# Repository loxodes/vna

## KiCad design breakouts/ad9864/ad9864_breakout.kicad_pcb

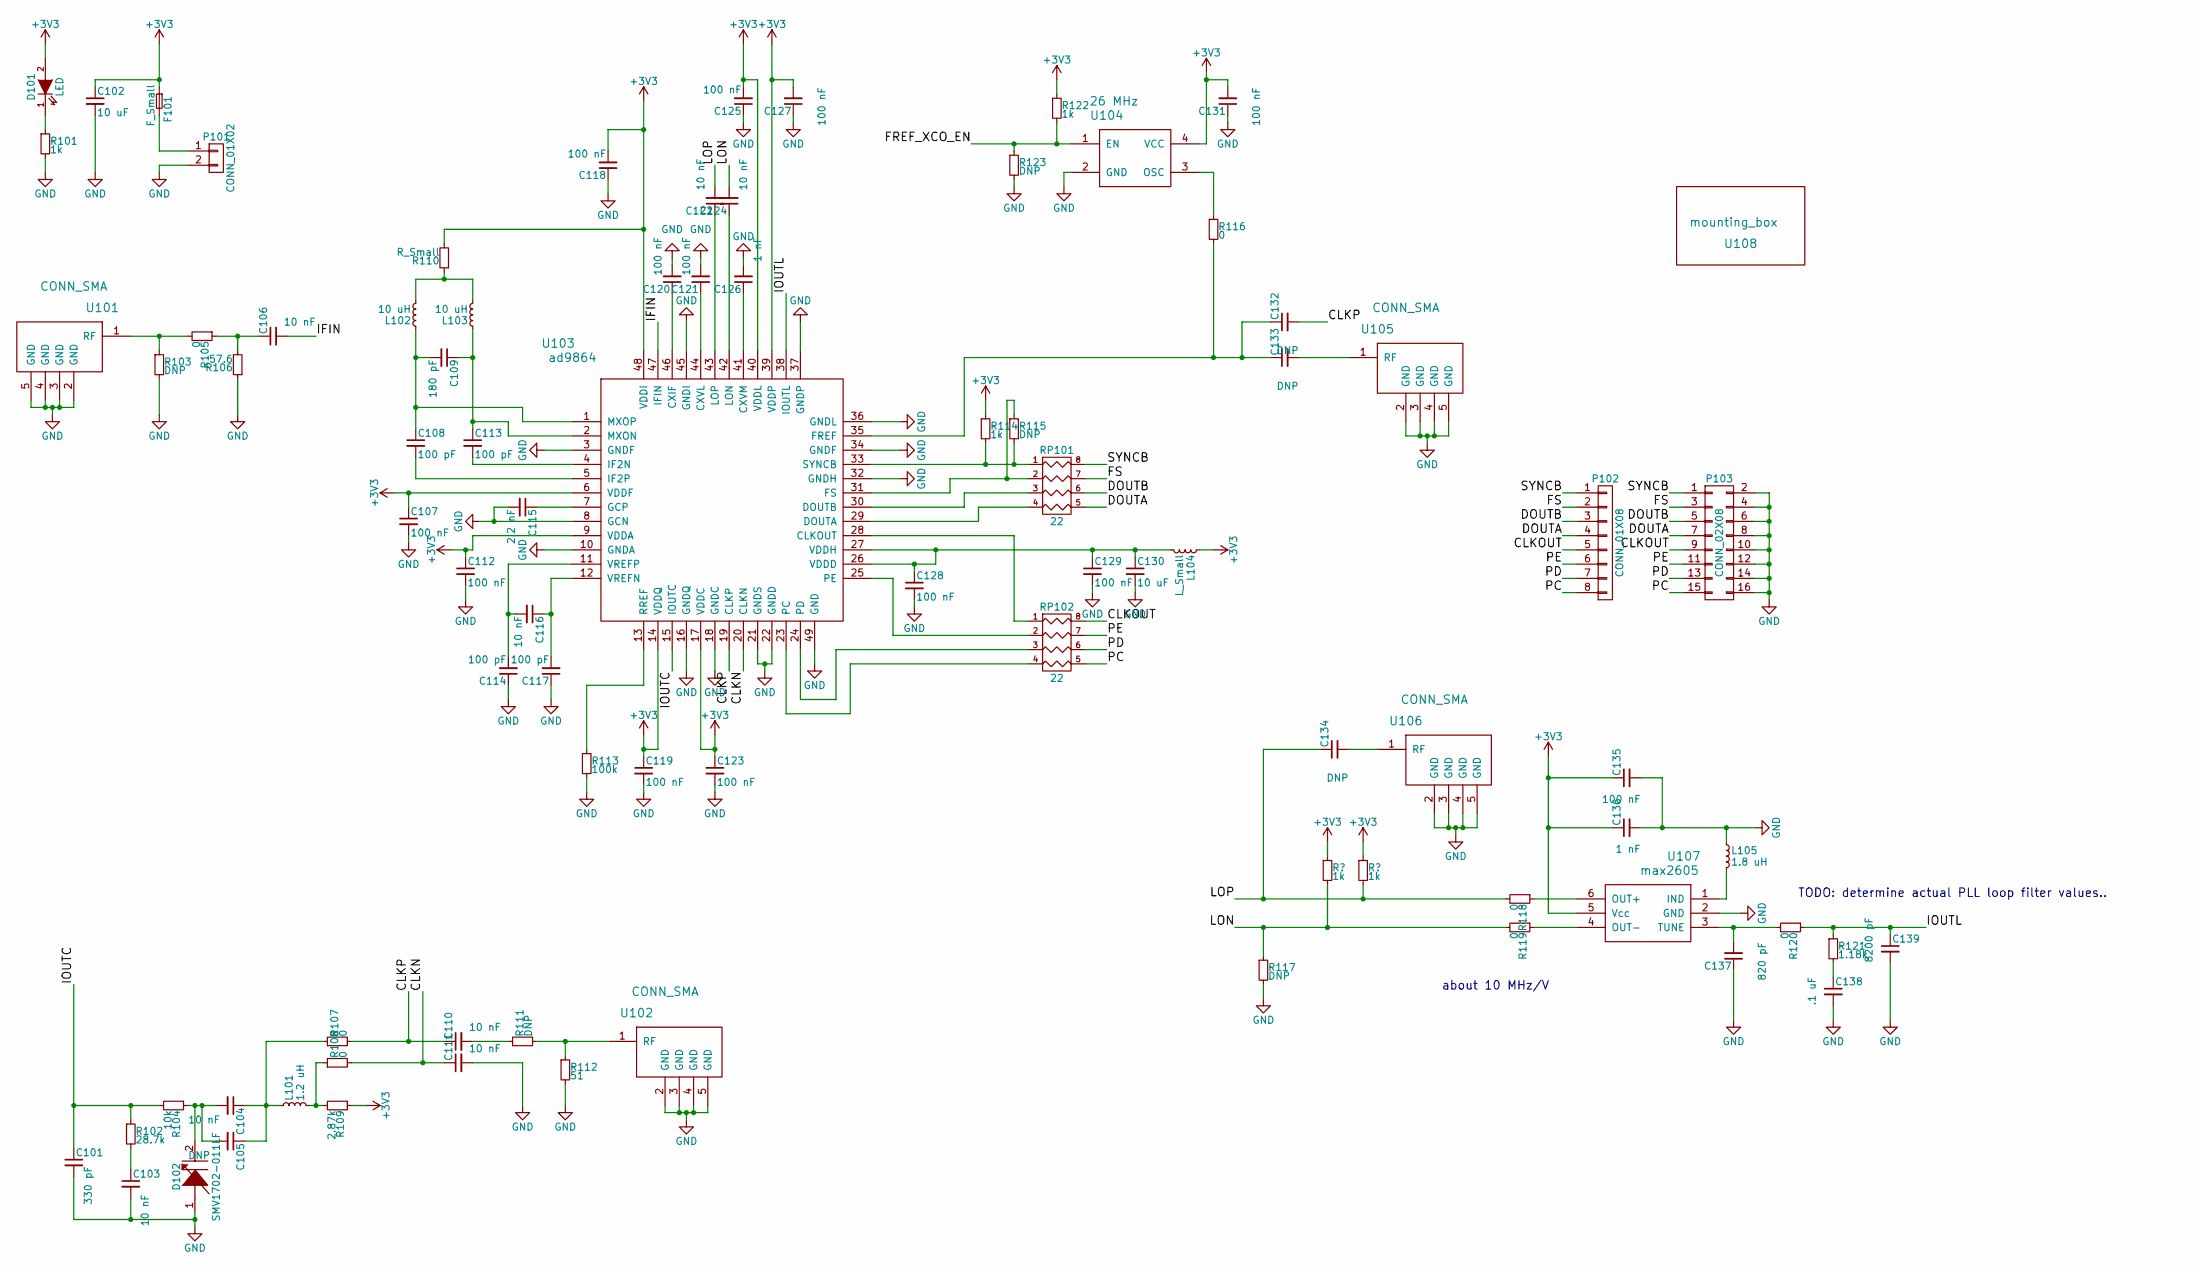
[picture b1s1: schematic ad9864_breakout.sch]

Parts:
C101: 330 pF; C_0603
C102, C130: 10 uF; C_0805
C103, C104, C106, C110, C111, C116, C122, C124: 10 nF; C_0603
C105, C132, C133, C134: DNP; C_0603
C107, C112, C118, C119, C120, C121, C123, C125, C127, C128, C129, C131, C135: 100 nF; C_0603
C108, C113, C114, C117: 100 pF; C_0603
C109: 180 pF; C_0603
C115: 2.2 nF; C_0603
C126, C136: 1 nF; C_0603
C137: 820 pF; C_0603
C138: .1 uF; C_0603
C139: 8200 pF; C_0603
D101: LED; LED_0603
D102: SMV1702-011LF; SOD-323
F101: F_Small; R_1812
L101: 1.2 uH; R_0805
L102, L103: 10 uH; R_0805
L104: L_Small; R_0603
L105: 1.8 uH; R_0805
P101: CONN_01X02; TerminalBlock_Pheonix_PT-3.5mm_2pol
P102: CONN_01X08; Pin_Header_Straight_1x08
P103: CONN_02X08; Pin_Header_Straight_2x08
R101, R114, R122: 1k; R_0603
R102: 28.7k; R_0603
R103, R111, R115, R117, R123: DNP; R_0603
R104: 10k; R_0603
R105, R107, R108, R116, R118, R119, R120: 0; R_0603
R106: 57.6; R_0603
R109: 2.87k; R_0603
R110: R_Small; R_0603
R112: 51; R_0603
R113: 100k; R_0603
R121: 1.18k; R_0603
RP101, RP102: 22; R_Array_Concave_4x0603
U101, U102, U105, U106: CONN_SMA; 732512200_SMA
U103: ad9864; QFN-48-1EP_7x7mm_Pitch0.5mm
U104: 26 MHz; crystal_FA238-TSX3225
U107: max2605; SOT-23-6
U108: mounting_box; momo

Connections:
+3V3: C102.1, C107.1, C112.1, C118.2, C119.1, C123.1, C125.2, C127.2, C131.2, C135.1, C136.1, D101.2 (A), F101.1, L104.1, R109.1, R110.2, R114.1, R122.1, U103.6 (VDDF), U103.9 (VDDA), U103.14 (VDDQ), U103.17 (VDDC), U103.39 (VDDP), U103.40 (VDDL), U103.48 (VDDI), U104.4 (VCC), U107.5 (Vcc)
/CLKN: C111.1, R108.2, U103.20 (CLKN)
/CLKOUT: P102.5, P103.9, RP102.8 (R1)
/CLKP: C110.1, C132.2, R107.2, U103.19 (CLKP)
/DOUTA: P102.4, P103.7, RP101.5 (R4)
/DOUTB: P102.3, P103.5, RP101.6 (R3)
/FREF_XCO_EN: R122.2, R123.1, U104.1 (EN)
/FS: P102.2, P103.3, RP101.7 (R2)
/IFIN: C106.2, U103.47 (IFIN)
/IOUTC: C101.1, R102.1, R104.2, U103.15 (IOUTC)
/IOUTL: C139.1, R120.1, R121.1, U103.38 (IOUTL)
/LON: C124.2, R117.1, R119.2
/LOP: C122.2, C134.1, R118.2
/PC: P102.8, P103.15, RP102.5 (R4)
/PD: P102.7, P103.13, RP102.6 (R3)
/PE: P102.6, P103.11, RP102.7 (R2)
/SYNCB: P102.1, P103.1, RP101.8 (R1)
GND: C101.2, C102.2, C103.2, C107.2, C111.2, C112.2, C114.1, C115.2, C117.1, C118.1, C119.2, C120.2, C121.2, C123.2, C125.1, C126.2, C127.1, C128.2, C129.2, C130.2, C131.1, C135.2, C136.2, C137.1, C138.2, C139.2, D102.1 (ANODE), L105.1, P101.2, P103.2, P103.4, P103.6, P103.8, P103.10, P103.12, P103.14, P103.16, R101.2, R103.2, R106.1, R112.2, R113.2, R117.2, R123.2, U101.2 (GND), U101.3 (GND), U101.4 (GND), U101.5 (GND), U102.2 (GND), U102.3 (GND), U102.4 (GND), U102.5 (GND), U103.3 (GNDF), U103.8 (GCN), U103.10 (GNDA), U103.16 (GNDQ), U103.18 (GNDC), U103.21 (GNDS), U103.22 (GNDD), U103.32 (GNDH), U103.34 (GNDF), U103.36 (GNDL), U103.37 (GNDP), U103.45 (GNDI), U103.49 (GND), U104.2 (GND), U105.2 (GND), U105.3 (GND), U105.4 (GND), U105.5 (GND), U106.2 (GND), U106.3 (GND), U106.4 (GND), U106.5 (GND), U107.2 (GND)
unnamed: C103.1, R102.2
unnamed: C104.1, C105.1, L101.1, R107.1
unnamed: C104.2, C105.2, D102.2 (CATHODE), R104.1
unnamed: C106.1, R105.1, R106.2
unnamed: C108.1, C109.2, L102.1, U103.1 (MXOP)
unnamed: C108.2, U103.5 (IF2P)
unnamed: C109.1, C113.1, L103.1, U103.2 (MXON)
unnamed: C110.2, R111.1
unnamed: C113.2, U103.4 (IF2N)
unnamed: C114.2, C116.2, U103.11 (VREFP)
unnamed: C115.1, U103.7 (GCP)
unnamed: C116.1, C117.2, U103.12 (VREFN)
unnamed: C120.1, U103.46 (CXIF)
unnamed: C121.1, U103.44 (CXVL)
unnamed: C122.1, U103.43 (LOP)
unnamed: C124.1, U103.42 (LON)
unnamed: C126.1, U103.41 (CXVM)
unnamed: C128.1, C129.1, C130.1, L104.2, U103.26 (VDDD), U103.27 (VDDH)
unnamed: C132.1, C133.1, R116.2, U103.35 (FREF)
unnamed: C133.2, U105.1 (RF)
unnamed: C134.2, U106.1 (RF)
unnamed: C137.2, R120.2, U107.3 (TUNE)
unnamed: C138.1, R121.2
unnamed: D101.1 (K), R101.1
unnamed: F101.2, P101.1
unnamed: L101.2, R108.1, R109.2
unnamed: L102.2, L103.2, R110.1
unnamed: L105.2, U107.1 (IND)
unnamed: R103.1, R105.2, U101.1 (RF)
unnamed: R111.2, R112.1, U102.1 (RF)
unnamed: R113.1, U103.13 (RREF)
unnamed: R114.2, R115.2, RP101.1, U103.33 (SYNCB)
unnamed: R115.1, RP101.2, U103.31 (FS)
unnamed: R116.1, U104.3 (OSC)
unnamed: R118.1, U107.6 (OUT+)
unnamed: R119.1, U107.4 (OUT-)
unnamed: RP101.3, U103.30 (DOUTB)
unnamed: RP101.4, U103.29 (DOUTA)
unnamed: RP102.1, U103.28 (CLKOUT)
unnamed: RP102.2, U103.25 (PE)
unnamed: RP102.3, U103.24 (PD)
unnamed: RP102.4, U103.23 (PC)

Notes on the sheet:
about 10 MHz/V
TODO: determine actual PLL loop filter values..

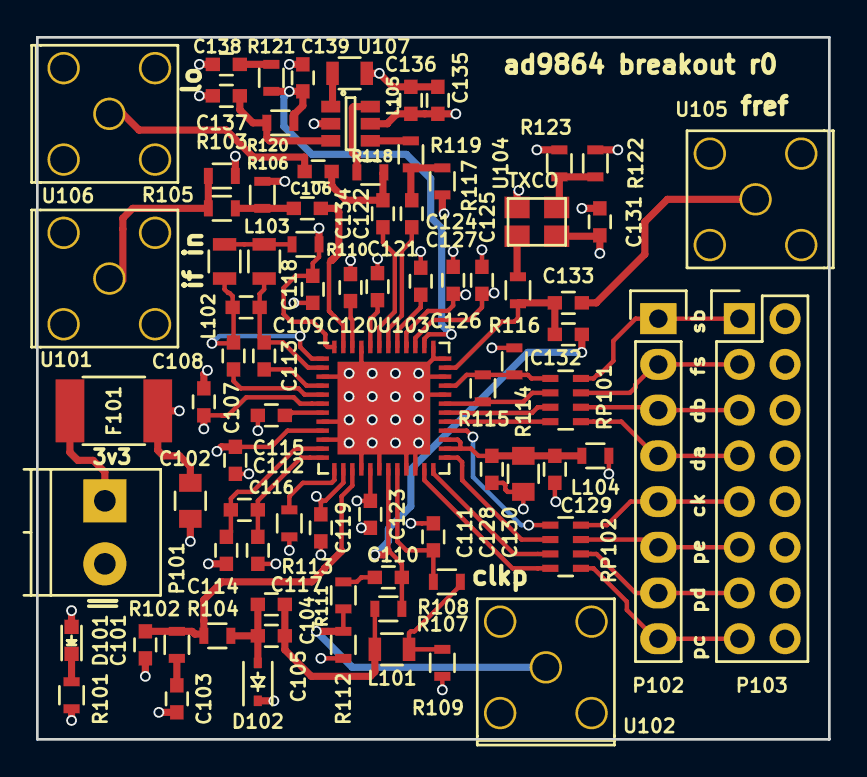
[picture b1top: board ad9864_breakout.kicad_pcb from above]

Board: 4 copper layers, 44.0 x 39.0 mm, 83 parts (1 on the bottom side), 60 nets.

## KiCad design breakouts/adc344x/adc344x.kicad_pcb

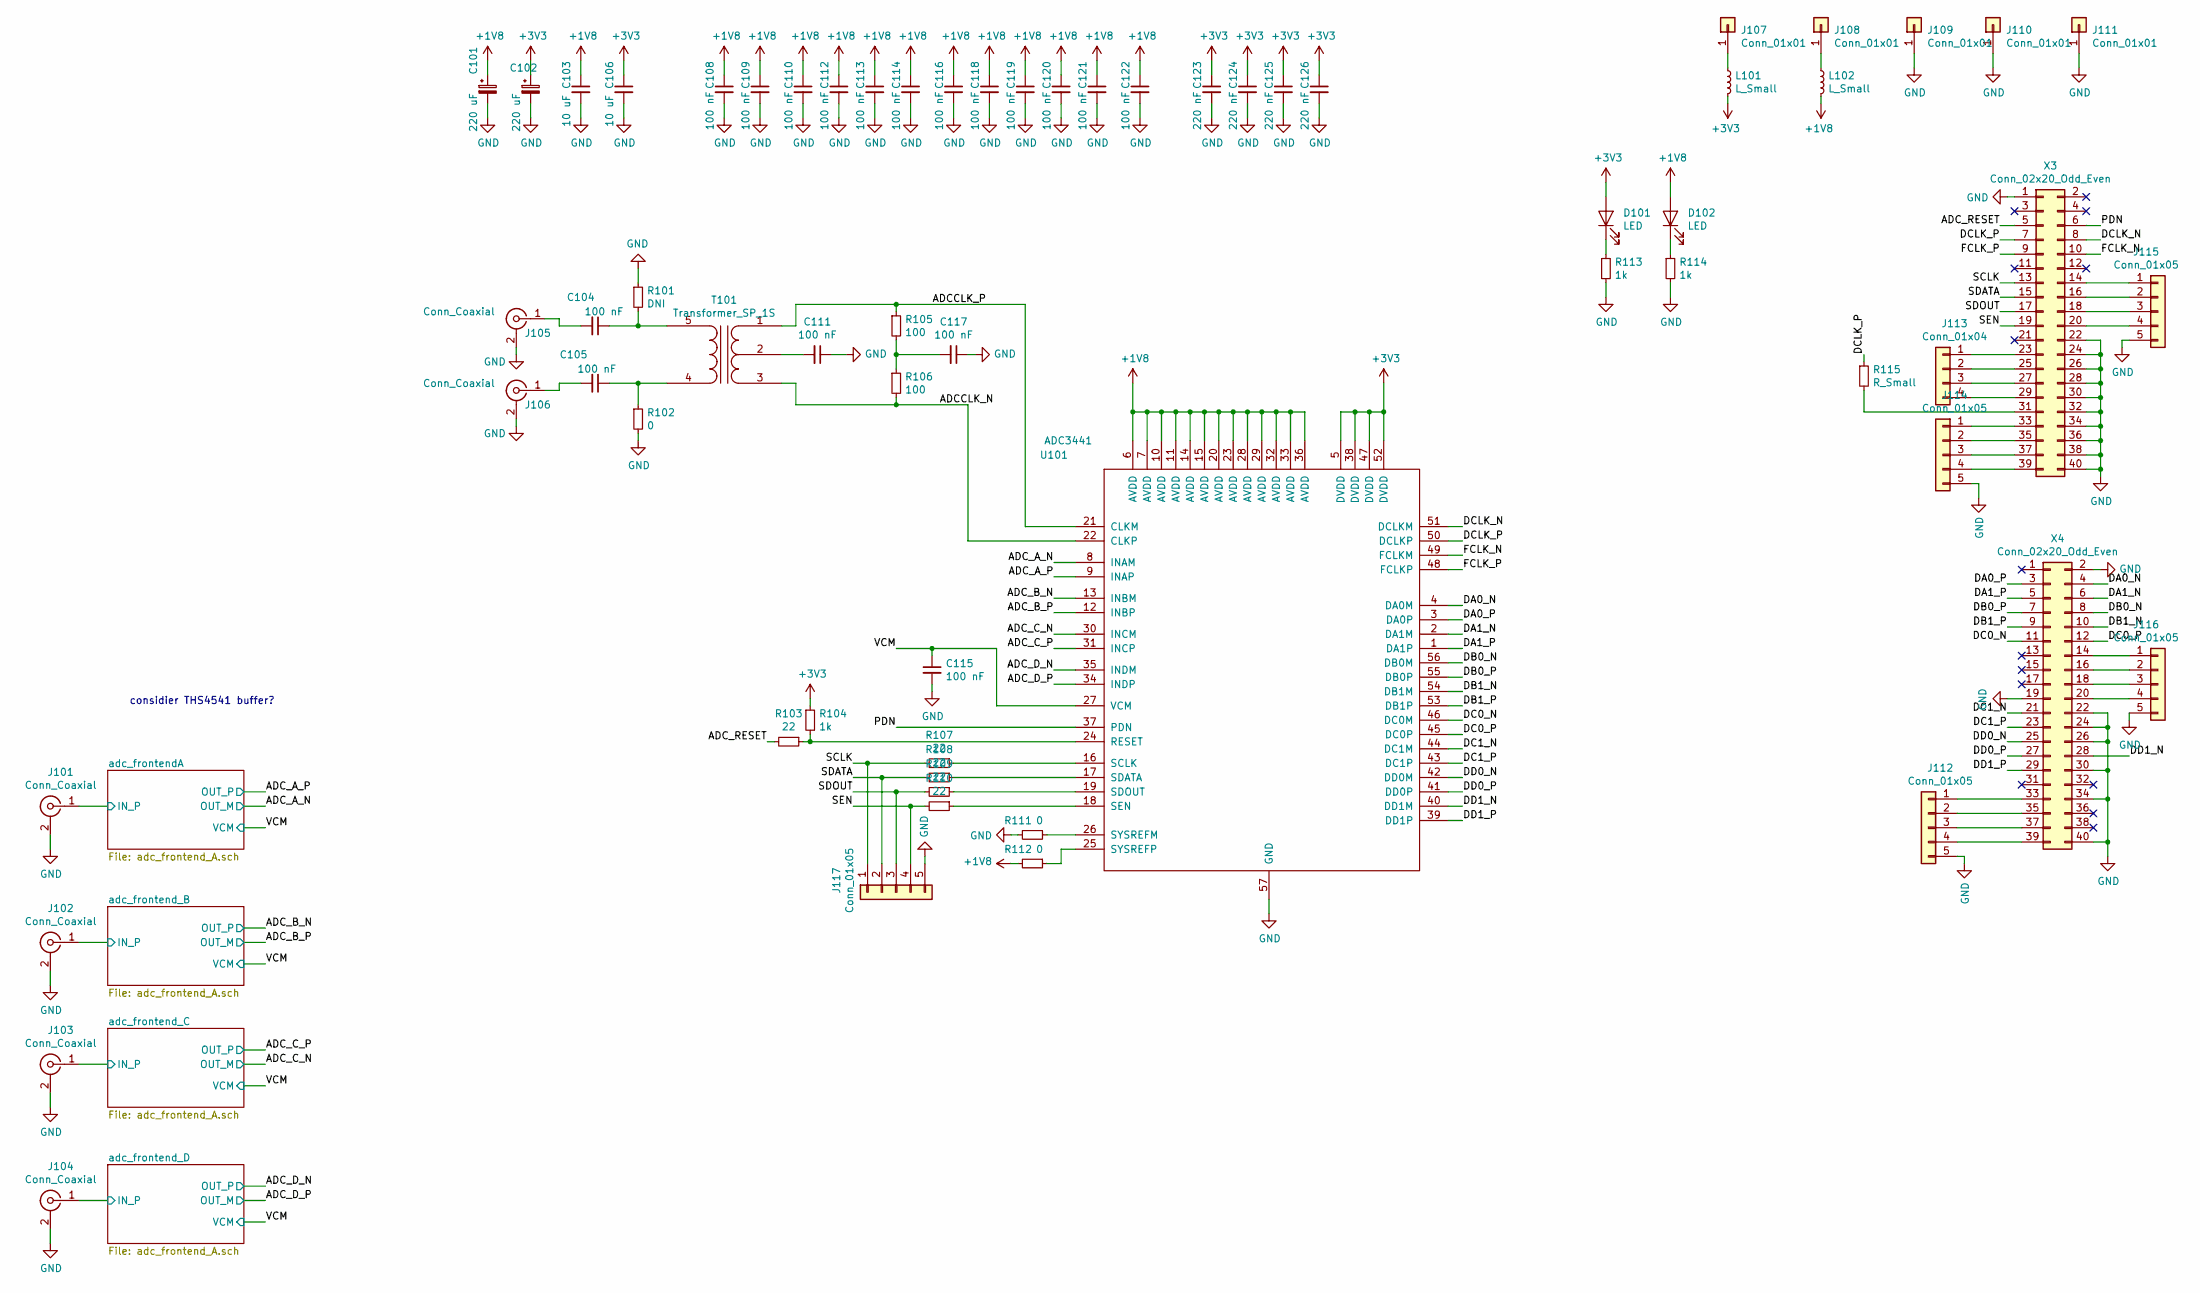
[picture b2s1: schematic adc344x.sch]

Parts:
C101, C102: 220 uF; c_elec_6.3x5.8
C103, C106: 10 uF; C_0603
C104, C105, C108, C109, C110, C111, C112, C113, C114, C115, C116, C117, C118, C119, C120, C121, C122: 100 nF; C_0402
C123, C124, C125, C126: 220 nF; C_0402
D101, D102: LED; LED_0603
J101, J102, J103, J104, J105, J106: Conn_Coaxial; 732512200_SMA
J107, J108, J109, J110, J111: Conn_01x01; TURRET_MILLMAX_2101
J112, J114, J115, J116, J117: Conn_01x05; Pin_Header_Straight_1x05
J113: Conn_01x04; Pin_Header_Straight_1x04
L101, L102: L_Small; R_0603
R101: DNI; R_0402
R102, R111, R112: 0; R_0402
R103, R107, R108, R109, R110: 22; R_0402
R104, R113, R114: 1k; R_0402
R105, R106: 100; R_0402
R115: R_Small; R_0402
T101: Transformer_SP_1S; 5LEAD_BALUN_4p83mm_3p3mm
U101: ADC3441; QFN-56_EP_8x8_Pitch0.5mm
X3, X4: Conn_02x20_Odd_Even; Pin_Header_Straight_2x20

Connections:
+1V8: C101.1, C103.1, C108.1, C109.1, C110.1, C112.1, C113.1, C114.1, C116.1, C118.1, C119.1, C120.1, C121.1, C122.1, D102.2 (A), L102.2, R112.2, U101.6 (AVDD), U101.7 (AVDD), U101.10 (AVDD), U101.11 (AVDD), U101.14 (AVDD), U101.15 (AVDD), U101.20 (AVDD), U101.23 (AVDD), U101.28 (AVDD), U101.29 (AVDD), U101.32 (AVDD), U101.33 (AVDD), U101.36 (AVDD)
+3V3: C102.1, C106.1, C123.1, C124.1, C125.1, C126.1, D101.2 (A), L101.2, R104.1, U101.5 (DVDD), U101.38 (DVDD), U101.47 (DVDD), U101.52 (DVDD)
/ADCCLK_N: R106.2, T101.3 (PR2), U101.22 (CLKP)
/ADCCLK_P: R105.1, T101.1 (PR1), U101.21 (CLKM)
/ADC_A_N: U101.8 (INAM); also elsewhere on the board
/ADC_A_P: U101.9 (INAP); also elsewhere on the board
/ADC_B_N: U101.13 (INBM); also elsewhere on the board
/ADC_B_P: U101.12 (INBP); also elsewhere on the board
/ADC_C_N: U101.30 (INCM); also elsewhere on the board
/ADC_C_P: U101.31 (INCP); also elsewhere on the board
/ADC_D_N: U101.35 (INDM); also elsewhere on the board
/ADC_D_P: U101.34 (INDP); also elsewhere on the board
/ADC_RESET: R103.2, X3.5
/DA0_N: U101.4 (DA0M), X4.4
/DA0_P: U101.3 (DA0P), X4.3
/DA1_N: U101.2 (DA1M), X4.6
/DA1_P: U101.1 (DA1P), X4.5
/DB0_N: U101.56 (DB0M), X4.8
/DB0_P: U101.55 (DB0P), X4.7
/DB1_N: U101.54 (DB1M), X4.10
/DB1_P: U101.53 (DB1P), X4.9
/DC0_N: U101.46 (DC0M), X4.11
/DC0_P: U101.45 (DC0P), X4.12
/DC1_N: U101.44 (DC1M), X4.21
/DC1_P: U101.43 (DC1P), X4.23
/DCLK_N: U101.51 (DCLKM), X3.8
/DCLK_P: R115.1, U101.50 (DCLKP), X3.7
/DD0_N: U101.42 (DD0M), X4.25
/DD0_P: U101.41 (DD0P), X4.27
/DD1_N: U101.40 (DD1M), X4.28
/DD1_P: U101.39 (DD1P), X4.29
/FCLK_N: U101.49 (FCLKM), X3.10
/FCLK_P: U101.48 (FCLKP), X3.9
/IN_P: J101.1 (In); also elsewhere on the board
/IN_P_1: J104.1 (In); also elsewhere on the board
/IN_P_2: J103.1 (In); also elsewhere on the board
/IN_P_3: J102.1 (In); also elsewhere on the board
/PDN: U101.37 (PDN), X3.6
/SCLK: J117.1, R107.2, X3.13
/SDATA: J117.2, R108.2, X3.15
/SDOUT: J117.3, R109.2, X3.17
/SEN: J117.4, R110.2, X3.19
/VCM: C115.1, U101.27 (VCM); also elsewhere on the board
GND: C101.2, C102.2, C103.2, C106.2, C108.2, C109.2, C110.2, C111.1, C112.2, C113.2, C114.2, C115.2, C116.2, C117.1, C118.2, C119.2, C120.2, C121.2, C122.2, C123.2, C124.2, C125.2, C126.2, J101.2 (Ext), J102.2 (Ext), J103.2 (Ext), J104.2 (Ext), J105.2 (Ext), J106.2 (Ext), J109.1, J110.1, J111.1, J112.5, J114.5, J115.5, J116.5, J117.5, R101.1, R102.2, R111.2, R113.2, R114.2, U101.57 (GND), X3.1, X3.22, X3.24, X3.26, X3.28, X3.30, X3.32, X3.34, X3.36, X3.38, X3.40, X4.2, X4.19, X4.22, X4.24, X4.26, X4.30, X4.34, X4.40; also elsewhere on the board
unnamed: C104.1, R101.2, T101.5 (S2)
unnamed: C104.2, J105.1 (In)
unnamed: C105.1, R102.1, T101.4 (S1)
unnamed: C105.2, J106.1 (In)
unnamed: C111.2, T101.2 (PM)
unnamed: C117.2, R105.2, R106.1
unnamed: D101.1 (K), R113.1
unnamed: D102.1 (K), R114.1
unnamed: J107.1, L101.1
unnamed: J108.1, L102.1
unnamed: J112.1, X4.33
unnamed: J112.2, X4.35
unnamed: J112.3, X4.37
unnamed: J112.4, X4.39
unnamed: J113.1, X3.23
unnamed: J113.2, X3.25
unnamed: J113.3, X3.27
unnamed: J113.4, X3.29
unnamed: J114.1, X3.33
unnamed: J114.2, X3.35
unnamed: J114.3, X3.37
unnamed: J114.4, X3.39
unnamed: J115.1, X3.14
unnamed: J115.2, X3.16
unnamed: J115.3, X3.18
unnamed: J115.4, X3.20
unnamed: J116.1, X4.14
unnamed: J116.2, X4.16
unnamed: J116.3, X4.18
unnamed: J116.4, X4.20
unnamed: R103.1, R104.2, U101.24 (RESET)
unnamed: R107.1, U101.16 (SCLK)
unnamed: R108.1, U101.17 (SDATA)
unnamed: R109.1, U101.19 (SDOUT)
unnamed: R110.1, U101.18 (SEN)
unnamed: R111.1, U101.26 (SYSREFM)
unnamed: R112.1, U101.25 (SYSREFP)
unnamed: R115.2, X3.31

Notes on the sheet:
considier THS4541 buffer?

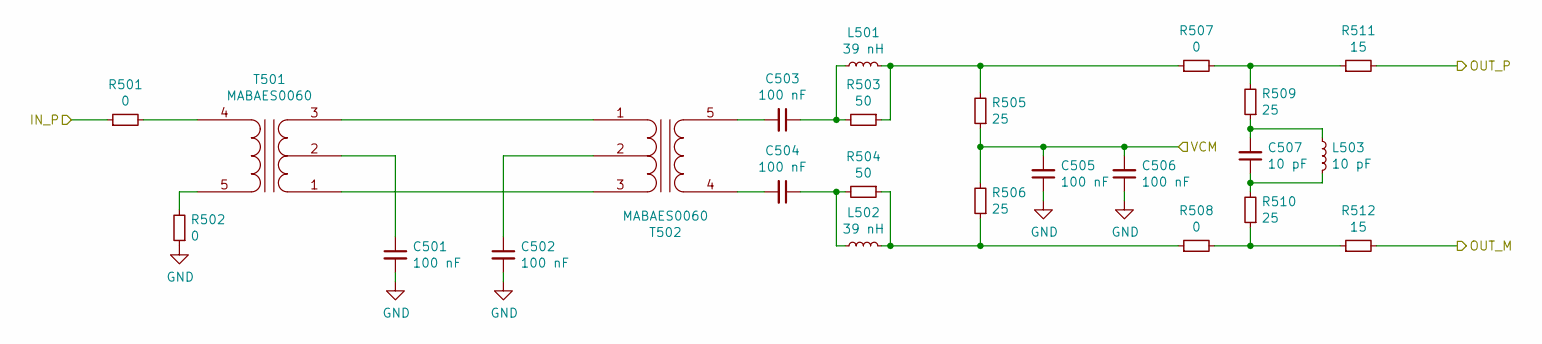
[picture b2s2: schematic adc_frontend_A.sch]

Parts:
C201, C202, C203, C204, C205, C206: 100 nF; C_0402
C207: 10 pF; C_0402
L201, L202: 39 nH; R_0402
L203: 10 pF; R_0402
R201, R202, R207, R208: 0; R_0402
R203, R204: 50; R_0402
R205, R206, R209, R210: 25; R_0402
R211, R212: 15; R_0402
T201, T202: MABAES0060; 5LEAD_BALUN_4p83mm_3p3mm

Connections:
/ADC_A_N: R212.2; also elsewhere on the board
/ADC_A_P: R211.2; also elsewhere on the board
/IN_P: R201.1; also elsewhere on the board
/VCM: C205.2, C206.2, R205.1, R206.2; also elsewhere on the board
GND: C201.2, C202.2, C205.1, C206.1, R202.1; also elsewhere on the board
unnamed: C201.1, T201.2 (PM)
unnamed: C202.1, T202.2 (PM)
unnamed: C203.1, L201.1, R203.2
unnamed: C203.2, T202.5 (S2)
unnamed: C204.1, L202.1, R204.2
unnamed: C204.2, T202.4 (S1)
unnamed: C207.1, L203.2, R210.2
unnamed: C207.2, L203.1, R209.1
unnamed: L201.2, R203.1, R205.2, R207.1
unnamed: L202.2, R204.1, R206.1, R208.1
unnamed: R201.2, T201.4 (S1)
unnamed: R202.2, T201.5 (S2)
unnamed: R207.2, R209.2, R211.1
unnamed: R208.2, R210.1, R212.1
unnamed: T201.1 (PR1), T202.3 (PR2)
unnamed: T201.3 (PR2), T202.1 (PR1)

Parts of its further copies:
C301, C302, C303, C304, C305, C306, C401, C402, C403, C404, C405, C406, C501, C502, C503, C504, C505, C506: 100 nF; C_0402
C307, C407, C507: 10 pF; C_0402
L301, L302, L401, L402, L501, L502: 39 nH; R_0402
L303, L403, L503: 10 pF; R_0402
R301, R302, R307, R308, R401, R402, R407, R408, R501, R502, R507, R508: 0; R_0402
R303, R304, R403, R404, R503, R504: 50; R_0402
R305, R306, R309, R310, R405, R406, R409, R410, R505, R506, R509, R510: 25; R_0402
R311, R312, R411, R412, R511, R512: 15; R_0402
T301, T302, T401, T402, T501, T502: MABAES0060; 5LEAD_BALUN_4p83mm_3p3mm

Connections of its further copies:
/ADC_B_N: R311.2; also elsewhere on the board
/ADC_B_P: R312.2; also elsewhere on the board
/ADC_C_N: R412.2; also elsewhere on the board
/ADC_C_P: R411.2; also elsewhere on the board
/ADC_D_N: R511.2; also elsewhere on the board
/ADC_D_P: R512.2; also elsewhere on the board
/IN_P_1: R501.1; also elsewhere on the board
/IN_P_2: R401.1; also elsewhere on the board
/IN_P_3: R301.1; also elsewhere on the board
/VCM: C305.2, C306.2, C405.2, C406.2, C505.2, C506.2, R305.1, R306.2, R405.1, R406.2, R505.1, R506.2; also elsewhere on the board
GND: C301.2, C302.2, C305.1, C306.1, C401.2, C402.2, C405.1, C406.1, C501.2, C502.2, C505.1, C506.1, R302.1, R402.1, R502.1; also elsewhere on the board
unnamed: C301.1, T301.2 (PM)
unnamed: C302.1, T302.2 (PM)
unnamed: C303.1, L301.1, R303.2
unnamed: C303.2, T302.5 (S2)
unnamed: C304.1, L302.1, R304.2
unnamed: C304.2, T302.4 (S1)
unnamed: C307.1, L303.2, R310.2
unnamed: C307.2, L303.1, R309.1
unnamed: C401.1, T401.2 (PM)
unnamed: C402.1, T402.2 (PM)
unnamed: C403.1, L401.1, R403.2
unnamed: C403.2, T402.5 (S2)
unnamed: C404.1, L402.1, R404.2
unnamed: C404.2, T402.4 (S1)
unnamed: C407.1, L403.2, R410.2
unnamed: C407.2, L403.1, R409.1
unnamed: C501.1, T501.2 (PM)
unnamed: C502.1, T502.2 (PM)
unnamed: C503.1, L501.1, R503.2
unnamed: C503.2, T502.5 (S2)
unnamed: C504.1, L502.1, R504.2
unnamed: C504.2, T502.4 (S1)
unnamed: C507.1, L503.2, R510.2
unnamed: C507.2, L503.1, R509.1
unnamed: L301.2, R303.1, R305.2, R307.1
unnamed: L302.2, R304.1, R306.1, R308.1
unnamed: L401.2, R403.1, R405.2, R407.1
unnamed: L402.2, R404.1, R406.1, R408.1
unnamed: L501.2, R503.1, R505.2, R507.1
unnamed: L502.2, R504.1, R506.1, R508.1
unnamed: R301.2, T301.4 (S1)
unnamed: R302.2, T301.5 (S2)
unnamed: R307.2, R309.2, R311.1
unnamed: R308.2, R310.1, R312.1
unnamed: R401.2, T401.4 (S1)
unnamed: R402.2, T401.5 (S2)
unnamed: R407.2, R409.2, R411.1
unnamed: R408.2, R410.1, R412.1
unnamed: R501.2, T501.4 (S1)
unnamed: R502.2, T501.5 (S2)
unnamed: R507.2, R509.2, R511.1
unnamed: R508.2, R510.1, R512.1
unnamed: T301.1 (PR1), T302.3 (PR2)
unnamed: T301.3 (PR2), T302.1 (PR1)
unnamed: T401.1 (PR1), T402.3 (PR2)
unnamed: T401.3 (PR2), T402.1 (PR1)
unnamed: T501.1 (PR1), T502.3 (PR2)
unnamed: T501.3 (PR2), T502.1 (PR1)

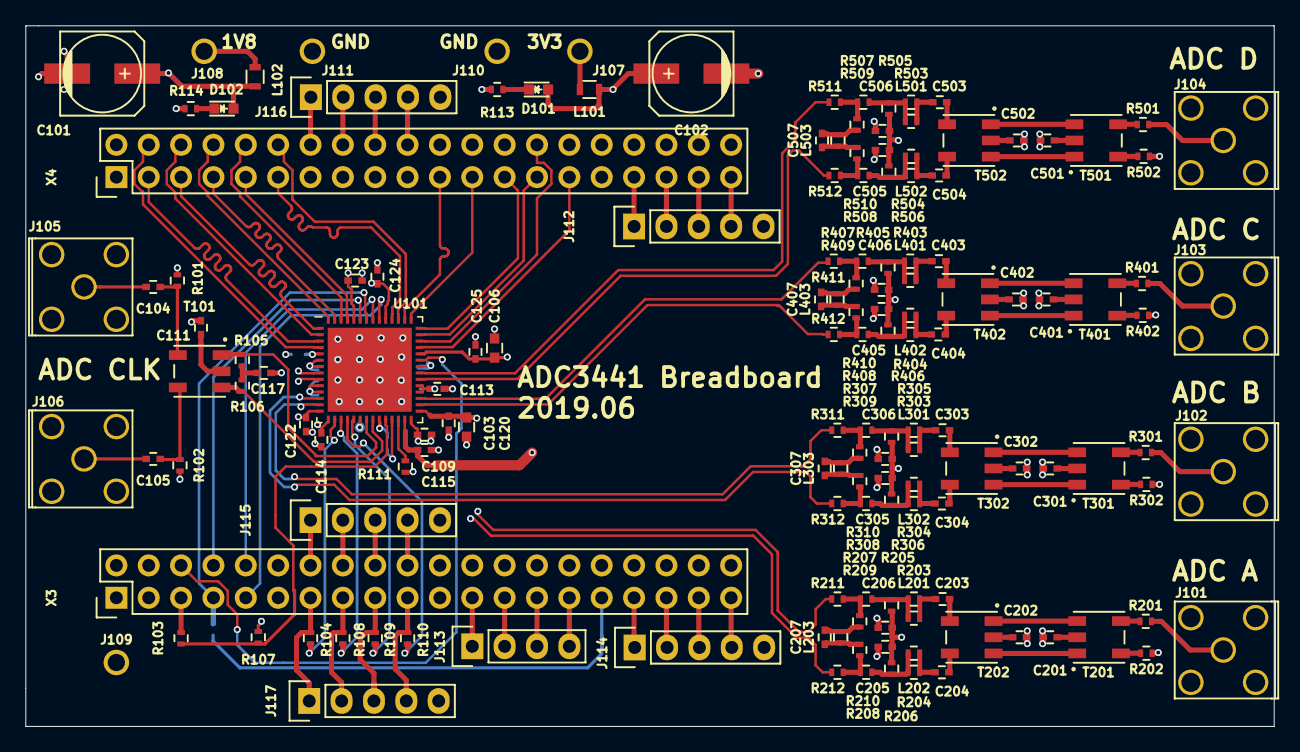
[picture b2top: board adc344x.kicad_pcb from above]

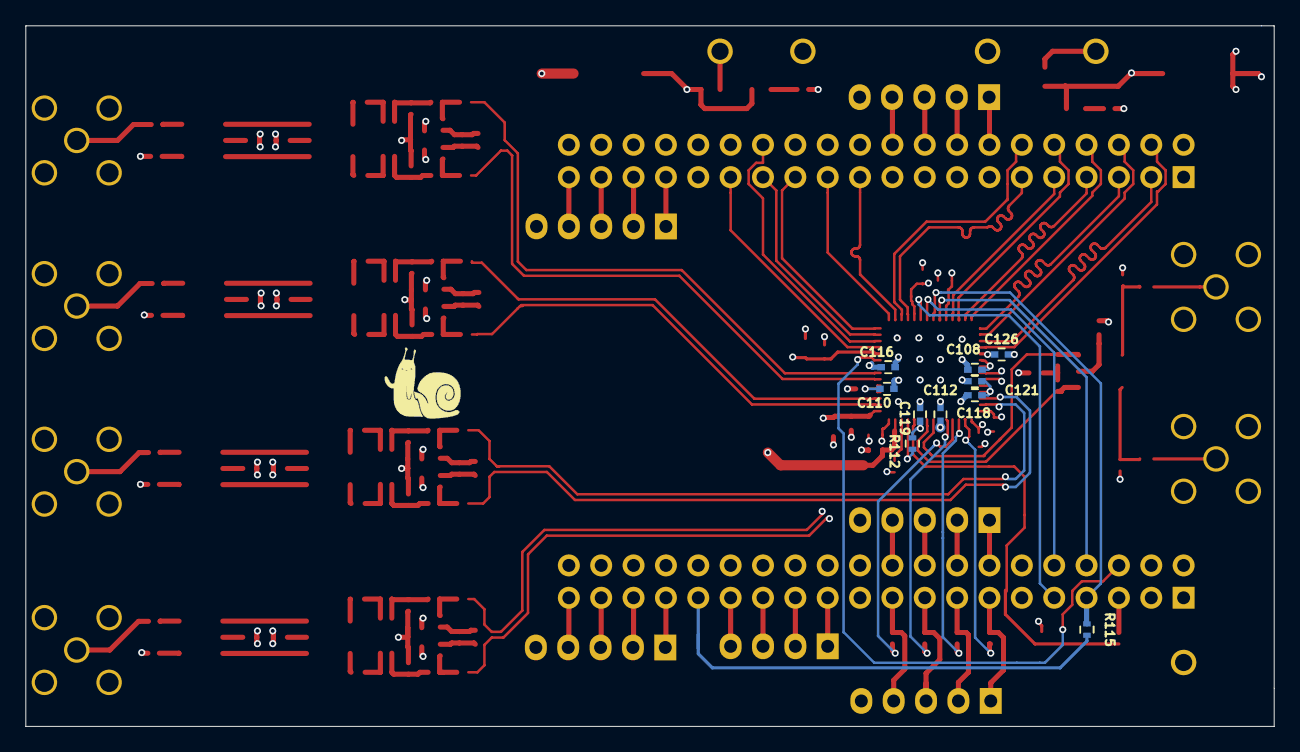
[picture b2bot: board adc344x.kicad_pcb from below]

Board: 4 copper layers, 98.0 x 55.0 mm, 161 parts (10 on the bottom side), 146 nets.

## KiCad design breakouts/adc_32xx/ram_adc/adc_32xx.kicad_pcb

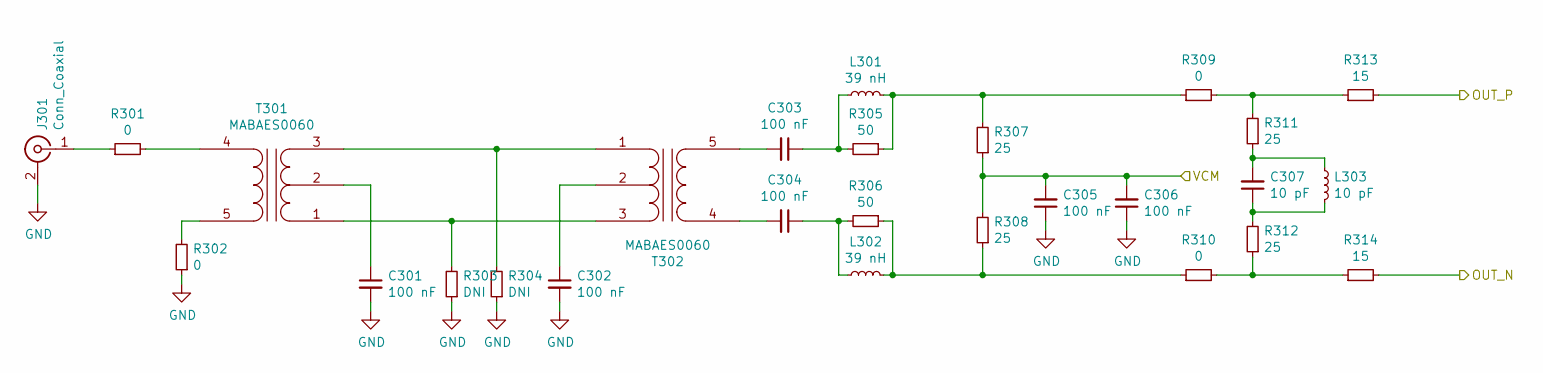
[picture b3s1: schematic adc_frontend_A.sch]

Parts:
C301, C302, C303, C304, C305, C306: 100 nF; C_0402_1005Metric
C307: 10 pF; C_0402_1005Metric
J301: Conn_Coaxial; 732512200_SMA
L301, L302: 39 nH; R_0402_1005Metric
L303: 10 pF; R_0402_1005Metric
R301, R302, R309, R310: 0; R_0402_1005Metric
R303, R304: DNI; R_0402_1005Metric
R305, R306: 50; R_0402_1005Metric
R307, R308, R311, R312: 25; R_0402_1005Metric
R313, R314: 15; R_0402_1005Metric
T301, T302: MABAES0060; 5LEAD_BALUN_4p83mm_3p3mm

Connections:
/VCM: C305.2, C306.2, R307.1, R308.2; also elsewhere on the board
/adc/IN_A_N: R314.2; also elsewhere on the board
/adc/IN_A_P: R313.2; also elsewhere on the board
GND: C301.2, C302.2, C305.1, C306.1, J301.2 (Ext), R302.1, R303.1, R304.1; also elsewhere on the board
unnamed: C301.1, T301.2 (PM)
unnamed: C302.1, T302.2 (PM)
unnamed: C303.1, L301.1, R305.2
unnamed: C303.2, T302.5 (S2)
unnamed: C304.1, L302.1, R306.2
unnamed: C304.2, T302.4 (S1)
unnamed: C307.1, L303.2, R312.2
unnamed: C307.2, L303.1, R311.1
unnamed: J301.1 (In), R301.1
unnamed: L301.2, R305.1, R307.2, R309.1
unnamed: L302.2, R306.1, R308.1, R310.1
unnamed: R301.2, T301.4 (S1)
unnamed: R302.2, T301.5 (S2)
unnamed: R303.2, T301.1 (PR1), T302.3 (PR2)
unnamed: R304.2, T301.3 (PR2), T302.1 (PR1)
unnamed: R309.2, R311.2, R313.1
unnamed: R310.2, R312.1, R314.1

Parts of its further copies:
C401, C402, C403, C404, C405, C406: 100 nF; C_0402_1005Metric
C407: 10 pF; C_0402_1005Metric
J401: Conn_Coaxial; 732512200_SMA
L401, L402: 39 nH; R_0402_1005Metric
L403: 10 pF; R_0402_1005Metric
R401, R402, R409, R410: 0; R_0402_1005Metric
R403, R404: DNI; R_0402_1005Metric
R405, R406: 50; R_0402_1005Metric
R407, R408, R411, R412: 25; R_0402_1005Metric
R413, R414: 15; R_0402_1005Metric
T401, T402: MABAES0060; 5LEAD_BALUN_4p83mm_3p3mm

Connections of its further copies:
/VCM: C405.2, C406.2, R407.1, R408.2; also elsewhere on the board
/adc/IN_B_N: R414.2; also elsewhere on the board
/adc/IN_B_P: R413.2; also elsewhere on the board
GND: C401.2, C402.2, C405.1, C406.1, J401.2 (Ext), R402.1, R403.1, R404.1; also elsewhere on the board
unnamed: C401.1, T401.2 (PM)
unnamed: C402.1, T402.2 (PM)
unnamed: C403.1, L401.1, R405.2
unnamed: C403.2, T402.5 (S2)
unnamed: C404.1, L402.1, R406.2
unnamed: C404.2, T402.4 (S1)
unnamed: C407.1, L403.2, R412.2
unnamed: C407.2, L403.1, R411.1
unnamed: J401.1 (In), R401.1
unnamed: L401.2, R405.1, R407.2, R409.1
unnamed: L402.2, R406.1, R408.1, R410.1
unnamed: R401.2, T401.4 (S1)
unnamed: R402.2, T401.5 (S2)
unnamed: R403.2, T401.1 (PR1), T402.3 (PR2)
unnamed: R404.2, T401.3 (PR2), T402.1 (PR1)
unnamed: R409.2, R411.2, R413.1
unnamed: R410.2, R412.1, R414.1

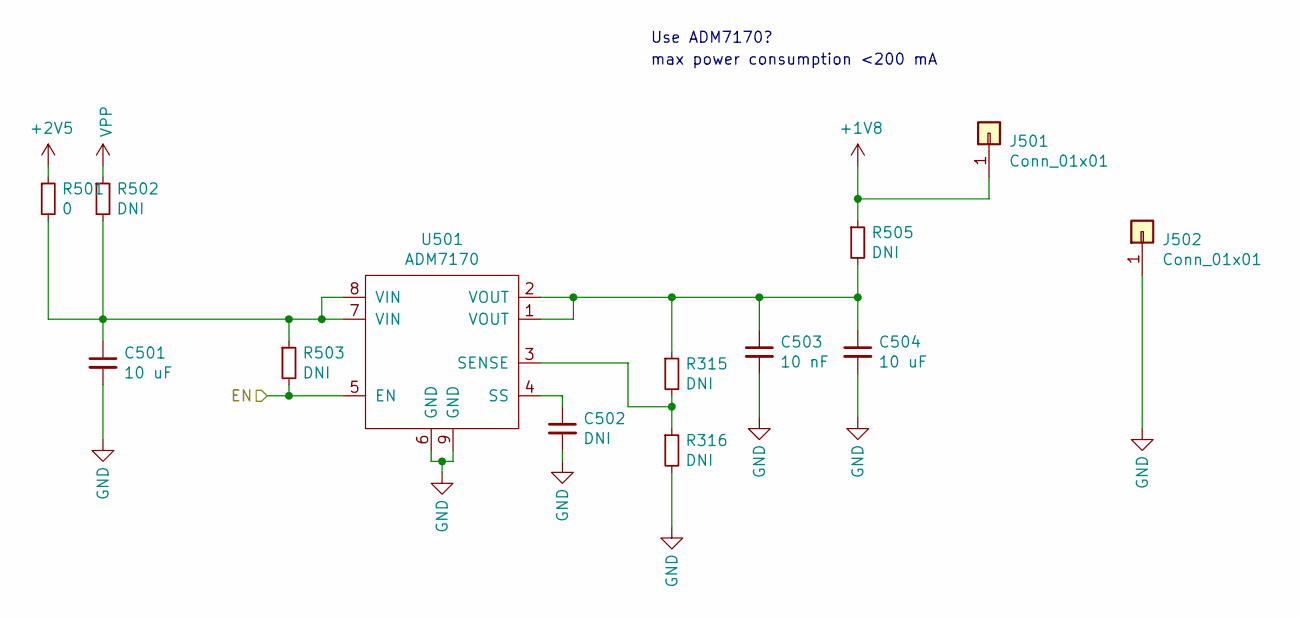
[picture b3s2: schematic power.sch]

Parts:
C501, C504: 10 uF; C_0603_1608Metric
C502: DNI; C_0402_1005Metric
C503: 10 nF; C_0402_1005Metric
J501, J502: Conn_01x01; TURRET_MILLMAX_2101
R315, R316, R502, R503, R505: DNI; R_0402_1005Metric
R501: 0; R_0402_1005Metric
U501: ADM7170; DFN-8-1EP_3x3mm_P0.5mm_EP1.66x2.38mm

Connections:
+1V8: J501.1, R505.1; also elsewhere on the board
+2V5: R501.1; also elsewhere on the board
/adc/EN: R503.2, U501.5 (EN); also elsewhere on the board
GND: C501.2, C502.2, C503.2, C504.2, J502.1, R316.2, U501.6 (GND), U501.9 (GND); also elsewhere on the board
unnamed: C501.1, R501.2, R502.2, R503.1, U501.7 (VIN), U501.8 (VIN)
unnamed: C502.1, U501.4 (SS)
unnamed: C503.1, C504.1, R315.1, R505.2, U501.1 (VOUT), U501.2 (VOUT)
unnamed: R315.2, R316.1, U501.3 (SENSE)
VPP: R502.1; also elsewhere on the board

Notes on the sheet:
max power consumption <200 mA
Use ADM7170?

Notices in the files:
parts and their libraries:
Copyright 2016 Accelerated Designs. All rights reserved.
